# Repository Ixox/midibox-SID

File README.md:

# midibox-SID
PCBs, Panels and firmware for puting a 4 stereo voices midiboxSid in a 1U 19" rack

Contains all files needed for this project : 
http://midibox.org/forums/topic/20008-midibox-sid-rack-1u-project/

SID_CS/
Kicad files for the 1st surface control PCB

SID_CS2/
Kicad files for the 2nd surface control PCB

SID_MB/
Kicad files for the mother board

SID_MIXER/
Kicad files for the mixer PCB

midibox_sid_v2_044_rack1U/
Firmware: Thorsten source code with some modification for the rack 1U PCBs

pfm2_lib.pretty/
Kicad library

shaeffer/
Front Panel Designer files that work with this 1U rack : 
http://www.frontpanels.de/nrg-case-19-enclosures/

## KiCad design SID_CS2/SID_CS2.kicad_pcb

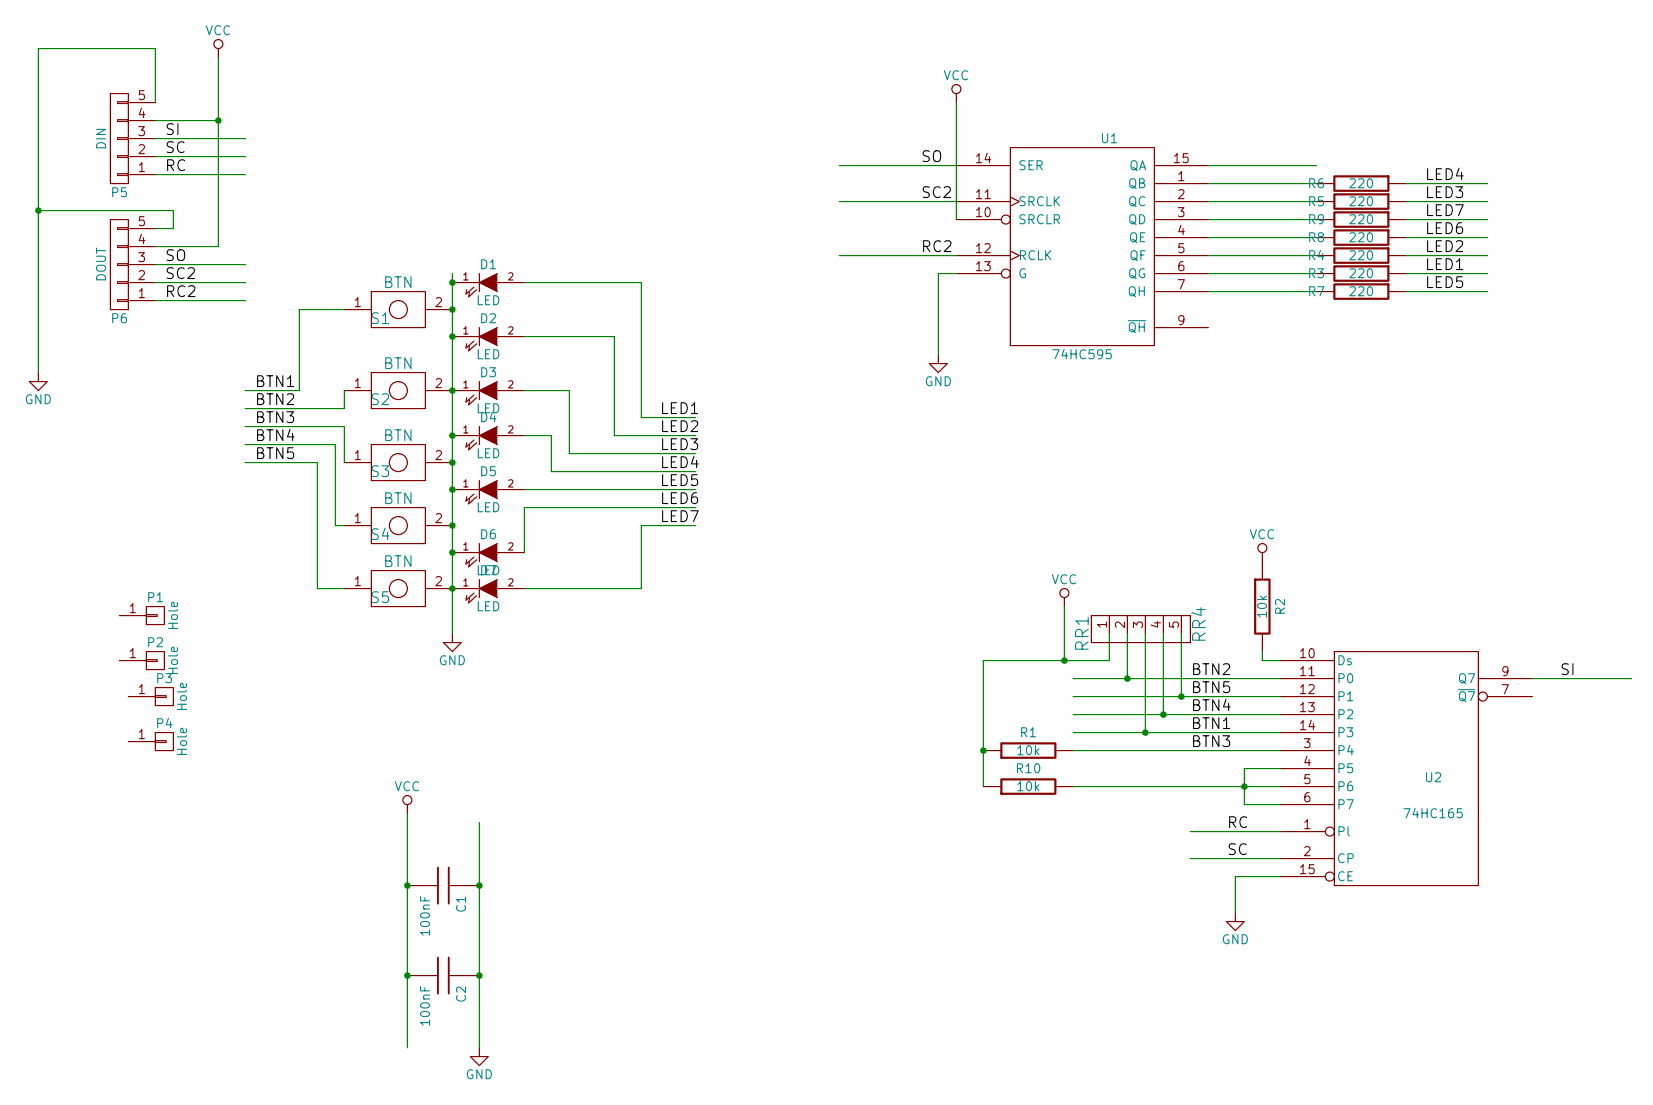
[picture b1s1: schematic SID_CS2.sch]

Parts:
C1, C2: 100nF; C_Disc_D3_P2.5
D1, D2, D3, D4, D5, D6, D7: LED; FMLed2
P1, P2, P3, P4: Hole; MountingHole_3.2mm_M3
P5: DIN; Pin_Header_Straight_1x05
P6: DOUT; Pin_Header_Straight_1x05
R1, R2, R10: 10k; Resistor_Horizontal_RM7mm
R3, R4, R5, R6, R7, R8, R9: 220; Resistor_Horizontal_RM7mm
RR1: RR4; Pin_Header_Straight_1x05
S1, S2, S3, S4, S5: BTN; FMButton2
U1: 74HC595; DIP-16_W7.62mm
U2: 74HC165; DIP-16_W7.62mm

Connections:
/BTN1: RR1.3, S1.1, U2.14 (P3)
/BTN2: RR1.2, S2.1, U2.11 (P0)
/BTN3: R1.2, S3.1, U2.3 (P4)
/BTN4: RR1.4, S4.1, U2.13 (P2)
/BTN5: RR1.5, S5.1, U2.12 (P1)
/LED1: D1.2 (A), R3.1
/LED2: D2.2 (A), R4.1
/LED3: D3.2 (A), R5.1
/LED4: D4.2 (A), R6.1
/LED5: D5.2 (A), R7.1
/LED6: D6.2 (A), R8.1
/LED7: D7.2 (A), R9.1
/RC: P5.1, U2.1 (Pl)
/RC2: P6.1, U1.12 (RCLK)
/SC: P5.2, U2.2 (CP)
/SC2: P6.2, U1.11 (SRCLK)
/SI: P5.3, U2.9 (Q7)
/SO: P6.3, U1.14 (SER)
GND: C1.1, C2.1, D1.1 (K), D2.1 (K), D3.1 (K), D4.1 (K), D5.1 (K), D6.1 (K), D7.1 (K), P5.5, P6.5, S1.2, S2.2, S3.2, S4.2, S5.2, U1.8 (GND), U1.13 (G), U2.8 (GND), U2.15 (CE)
unnamed: R2.2, U2.10 (Ds)
unnamed: R3.2, U1.6 (QG)
unnamed: R4.2, U1.5 (QF)
unnamed: R5.2, U1.2 (QC)
unnamed: R6.2, U1.1 (QB)
unnamed: R7.2, U1.7 (QH)
unnamed: R8.2, U1.4 (QE)
unnamed: R9.2, U1.3 (QD)
unnamed: R10.2, U2.4 (P5), U2.5 (P6), U2.6 (P7)
VCC: C1.2, C2.2, P5.4, P6.4, R1.1, R2.1, R10.1, RR1.1, U1.10 (SRCLR), U1.16 (VCC), U2.16 (VCC)

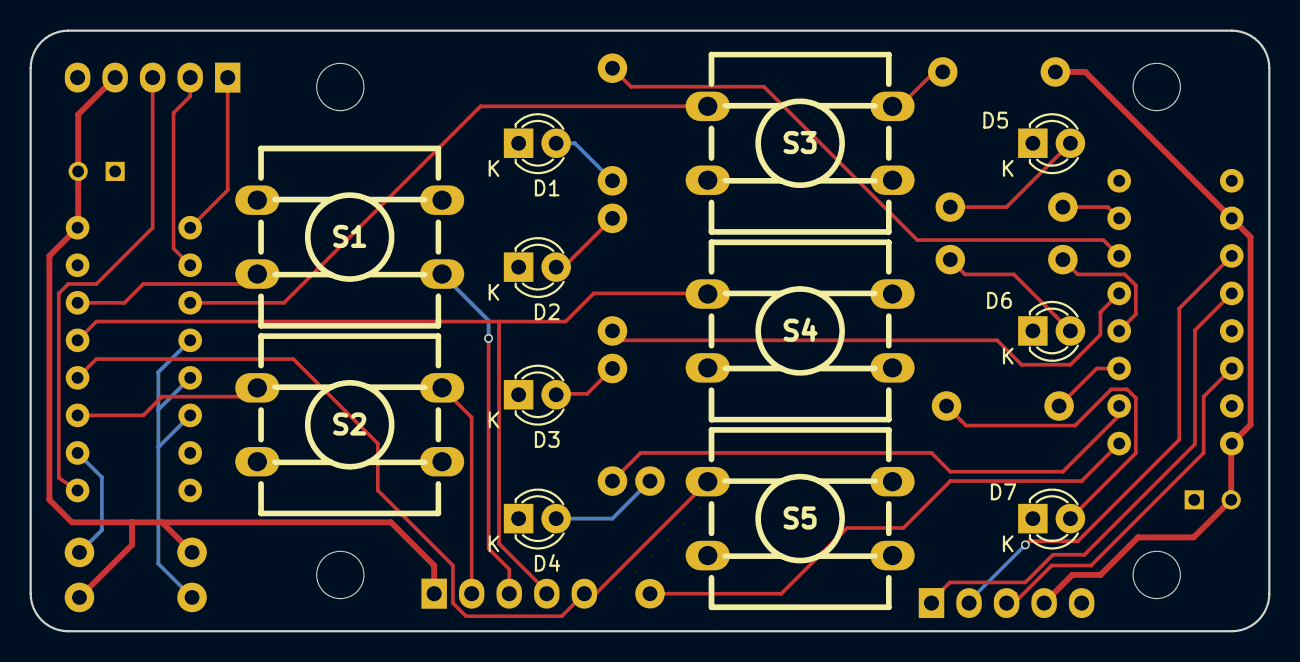
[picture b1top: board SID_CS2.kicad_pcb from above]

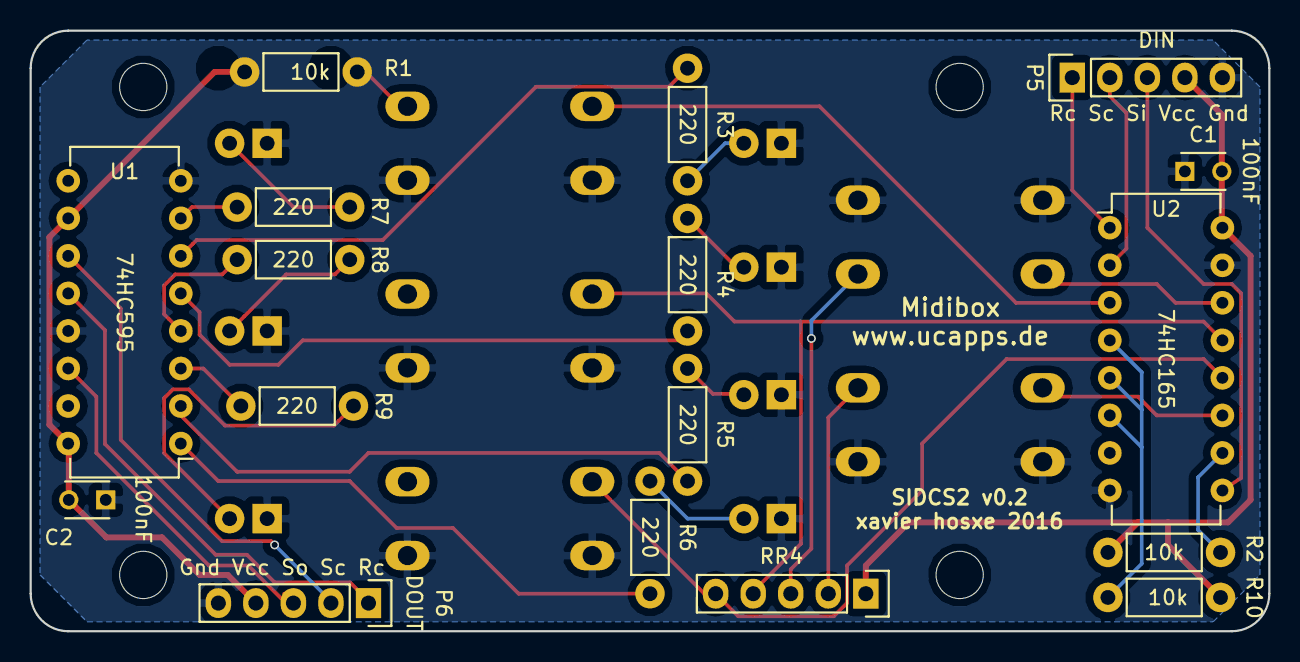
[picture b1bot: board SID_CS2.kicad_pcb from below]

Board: 2 copper layers, 83.8 x 40.6 mm, 33 parts (17 on the bottom side), 29 nets.

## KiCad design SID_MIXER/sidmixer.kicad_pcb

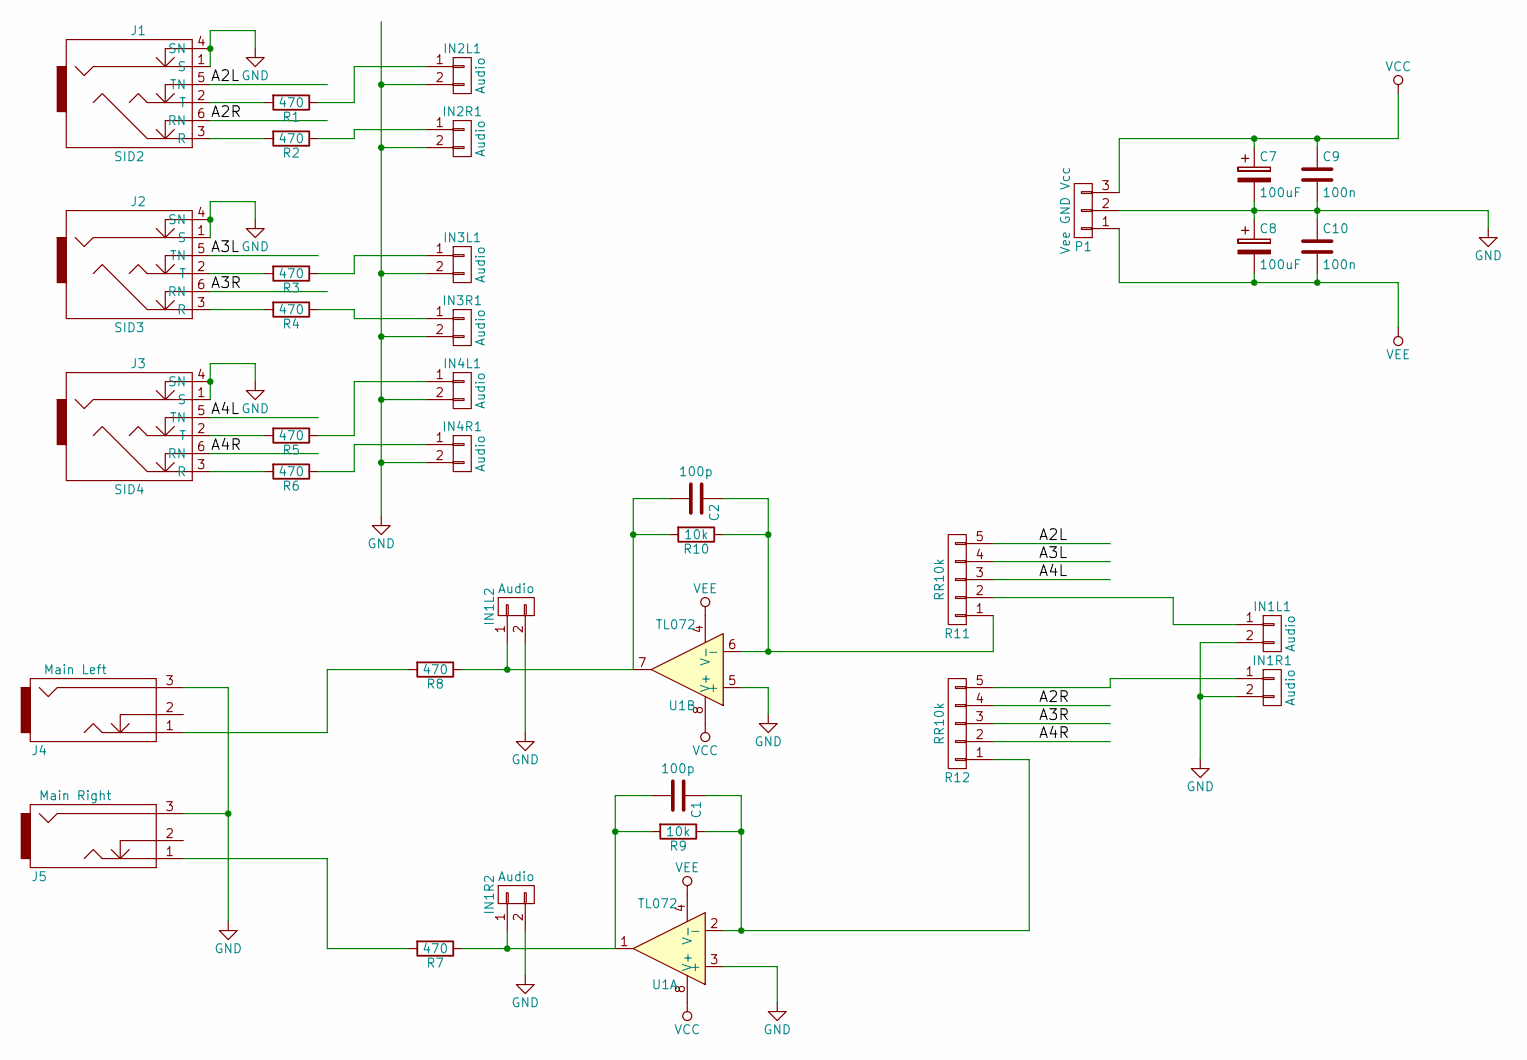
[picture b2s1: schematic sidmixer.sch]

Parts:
C1, C2: 100p; C_Disc_D3_P2.5
C7, C8: 100uF; C_Radial_D6.3_L11.2_P2.5
C9, C10: 100n; C_Disc_D3_P2.5
IN1L1, IN1L2, IN1R1, IN1R2, IN2L1, IN2R1, IN3L1, IN3R1, IN4L1, IN4R1: Audio; Pin_Header_Straight_1x02
J1: SID2; NRJ6HF
J2: SID3; NRJ6HF
J3: SID4; NRJ6HF
J4: Main Left; NRJ4HF
J5: Main Right; NRJ4HF
P1: Vee GND Vcc; Pin_Header_Straight_1x03
R1, R2, R3, R4, R5, R6, R7, R8: 470; Resistor_Horizontal_RM7mm
R9, R10: 10k; Resistor_Horizontal_RM7mm
R11, R12: RR10k; FMRR
U1: TL072; DIP-8_W7.62mm

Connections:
/A2L: J1.5 (TN), R11.5
/A2R: J1.6 (RN), R12.4
/A3L: J2.5 (TN), R11.4
/A3R: J2.6 (RN), R12.3
/A4L: J3.5 (TN), R11.3
/A4R: J3.6 (RN), R12.2
GND: C7.2, C8.1, C9.2, C10.1, IN1L1.2, IN1L2.2, IN1R1.2, IN1R2.2, IN2L1.2, IN2R1.2, IN3L1.2, IN3R1.2, IN4L1.2, IN4R1.2, J1.1 (S), J1.4 (SN), J2.1 (S), J2.4 (SN), J3.1 (S), J3.4 (SN), J4.3, J5.3, P1.2, U1.3 (+), U1.5 (+)
unnamed: C1.1, R9.1, R12.1, U1.2 (-)
unnamed: C1.2, IN1R2.1, R7.1, R9.2, U1.1
unnamed: C2.1, R10.1, R11.1, U1.6 (-)
unnamed: C2.2, IN1L2.1, R8.1, R10.2, U1.7
unnamed: IN1L1.1, R11.2
unnamed: IN1R1.1, R12.5
unnamed: IN2L1.1, R1.1
unnamed: IN2R1.1, R2.1
unnamed: IN3L1.1, R3.1
unnamed: IN3R1.1, R4.1
unnamed: IN4L1.1, R5.1
unnamed: IN4R1.1, R6.1
unnamed: J1.2 (T), R1.2
unnamed: J1.3 (R), R2.2
unnamed: J2.2 (T), R3.2
unnamed: J2.3 (R), R4.2
unnamed: J3.2 (T), R5.2
unnamed: J3.3 (R), R6.2
unnamed: J4.1, R8.2
unnamed: J5.1, R7.2
VCC: C7.1, C9.1, P1.3, U1.8 (V+)
VEE: C8.2, C10.2, P1.1, U1.4 (V-)

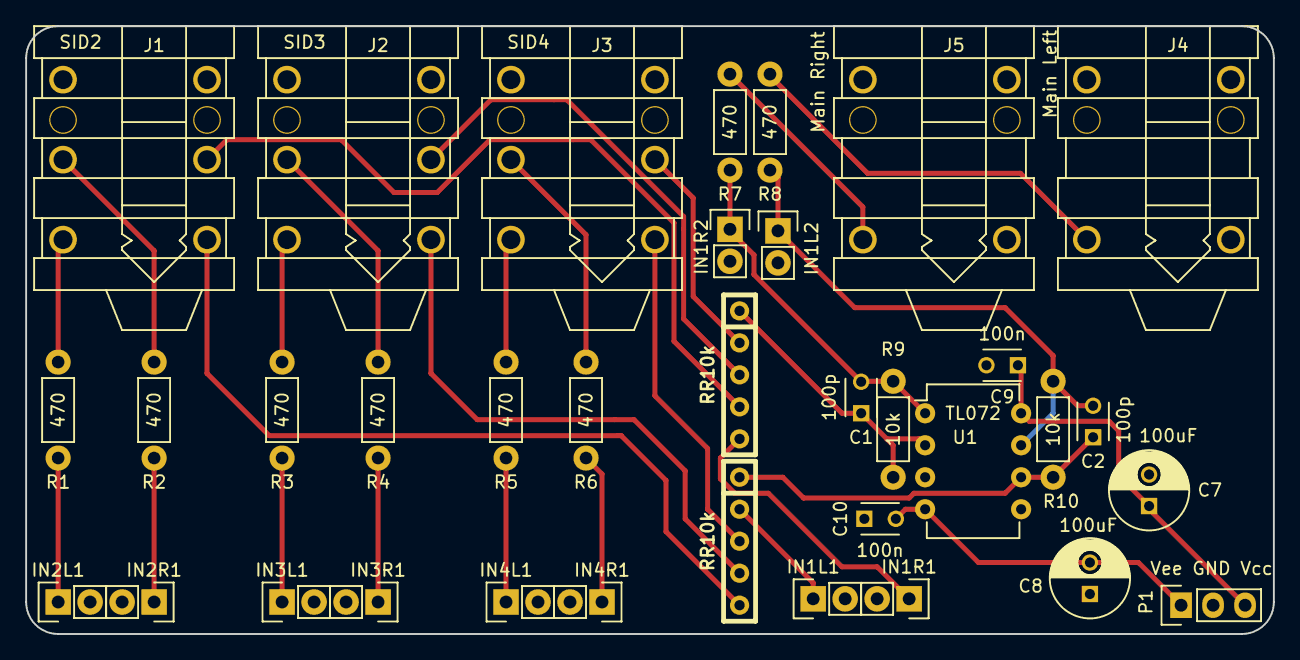
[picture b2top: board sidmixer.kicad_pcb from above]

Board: 2 copper layers, 99.1 x 48.3 mm, 35 parts (0 on the bottom side), 29 nets.

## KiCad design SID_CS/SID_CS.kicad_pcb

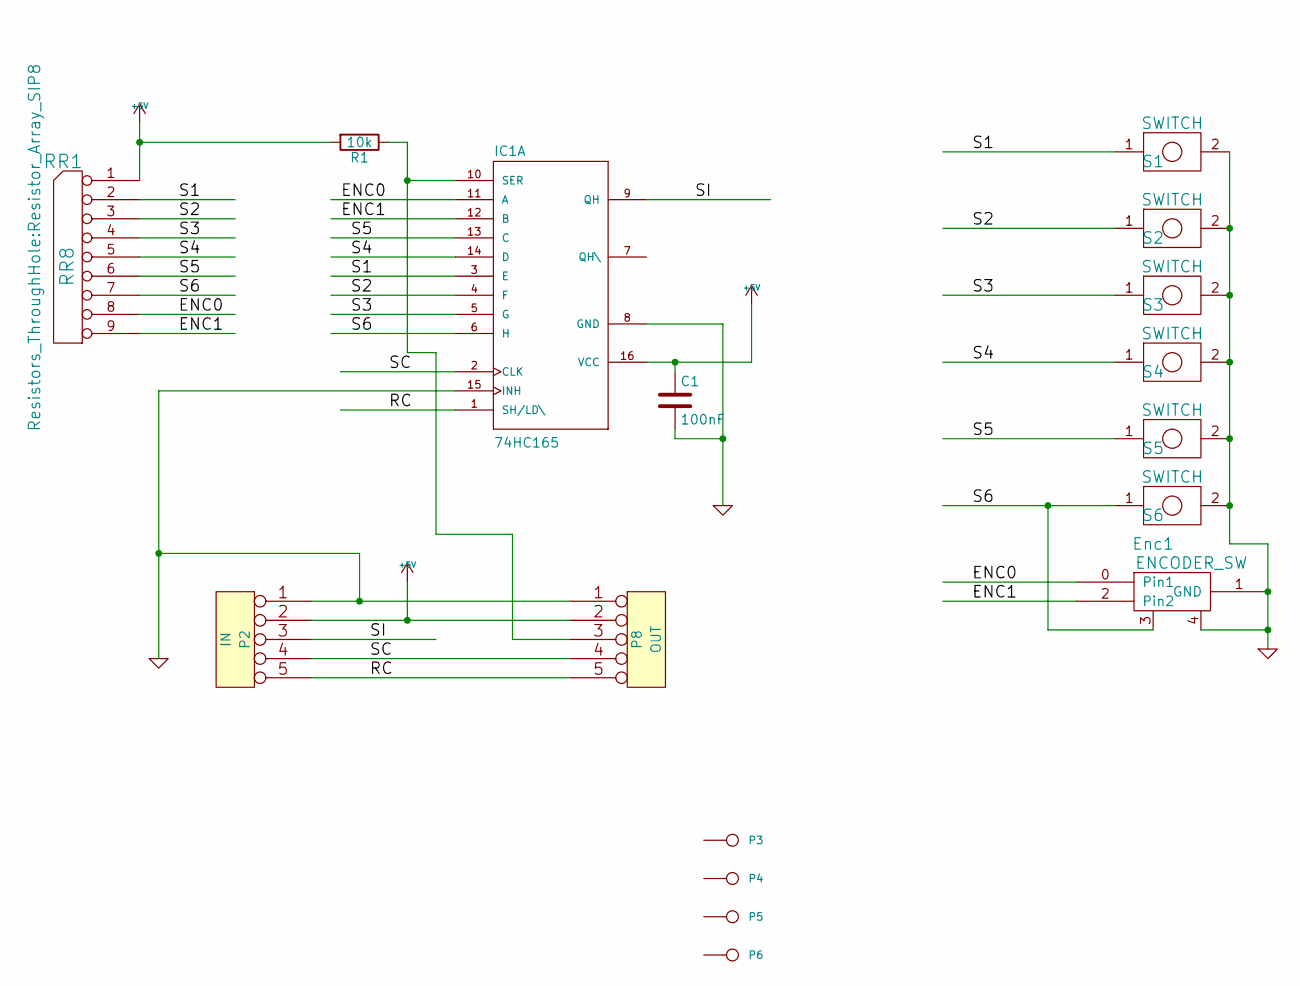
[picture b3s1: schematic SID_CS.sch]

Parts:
C1: 100nF; C_Disc_D3_P2.5
Enc1: ENCODER_SW; FMEncoderWithSwitch2
IC1: 74HC165; DIP-16_W7.62mm_LongPads
P2: IN; Pin_Header_Straight_1x05
P3, P4, P5, P6: CONN_1; MountingHole_3.2mm_M3
P8: OUT; Pin_Header_Straight_1x05
R1: 10k; Resistor_Horizontal_RM7mm
RR1: RR8; Resistor_Array_SIP8
S1, S2, S3, S4, S5, S6: SWITCH; FMButton2

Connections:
+5V: C1.1, IC1.16 (VCC), P2.2, P8.2, R1.2, RR1.1 (COM)
/ENC0: Enc1.0 (Pin1), IC1.11 (A), RR1.8
/ENC1: Enc1.2 (Pin2), IC1.12 (B), RR1.9
/RC: IC1.1 (SH/LD\), P2.5, P8.5
/S1: IC1.3 (E), RR1.2, S1.1
/S2: IC1.4 (F), RR1.3, S2.1
/S3: IC1.5 (G), RR1.4, S3.1
/S4: IC1.14 (D), RR1.5, S4.1
/S5: IC1.13 (C), RR1.6, S5.1
/S6: Enc1.3, IC1.6 (H), RR1.7, S6.1
/SC: IC1.2 (CLK), P2.4, P8.4
/SI: IC1.9 (QH), P2.3
GND: C1.2, Enc1.1 (GND), Enc1.4, IC1.8 (GND), IC1.15 (INH), P2.1, P8.1, S1.2, S2.2, S3.2, S4.2, S5.2, S6.2
unnamed: IC1.10 (SER), P8.3, R1.1

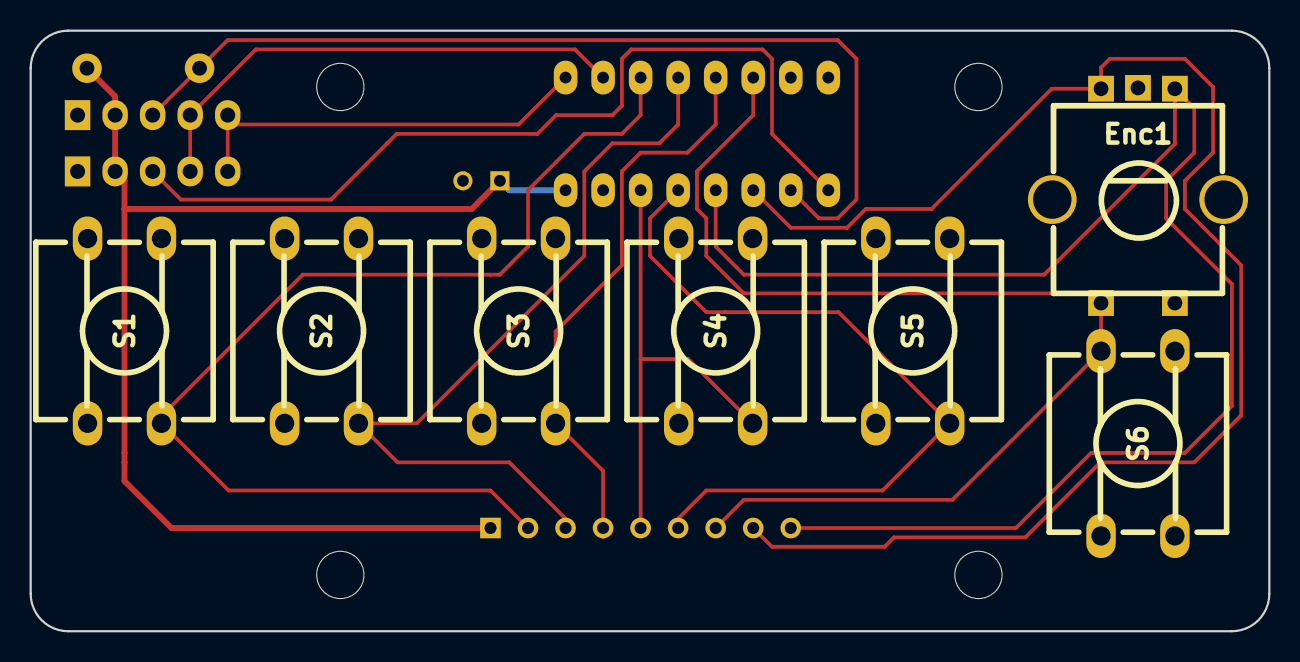
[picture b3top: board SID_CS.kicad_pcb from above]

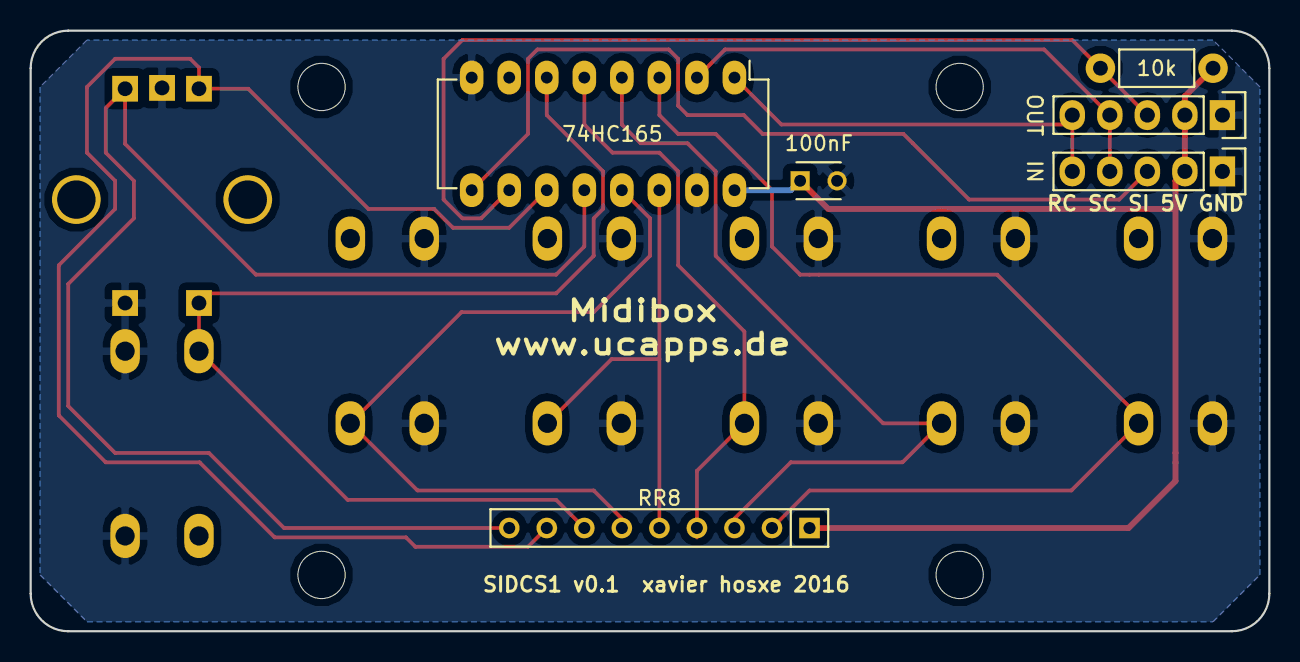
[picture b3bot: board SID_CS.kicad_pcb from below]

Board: 2 copper layers, 83.8 x 40.6 mm, 17 parts (6 on the bottom side), 14 nets.

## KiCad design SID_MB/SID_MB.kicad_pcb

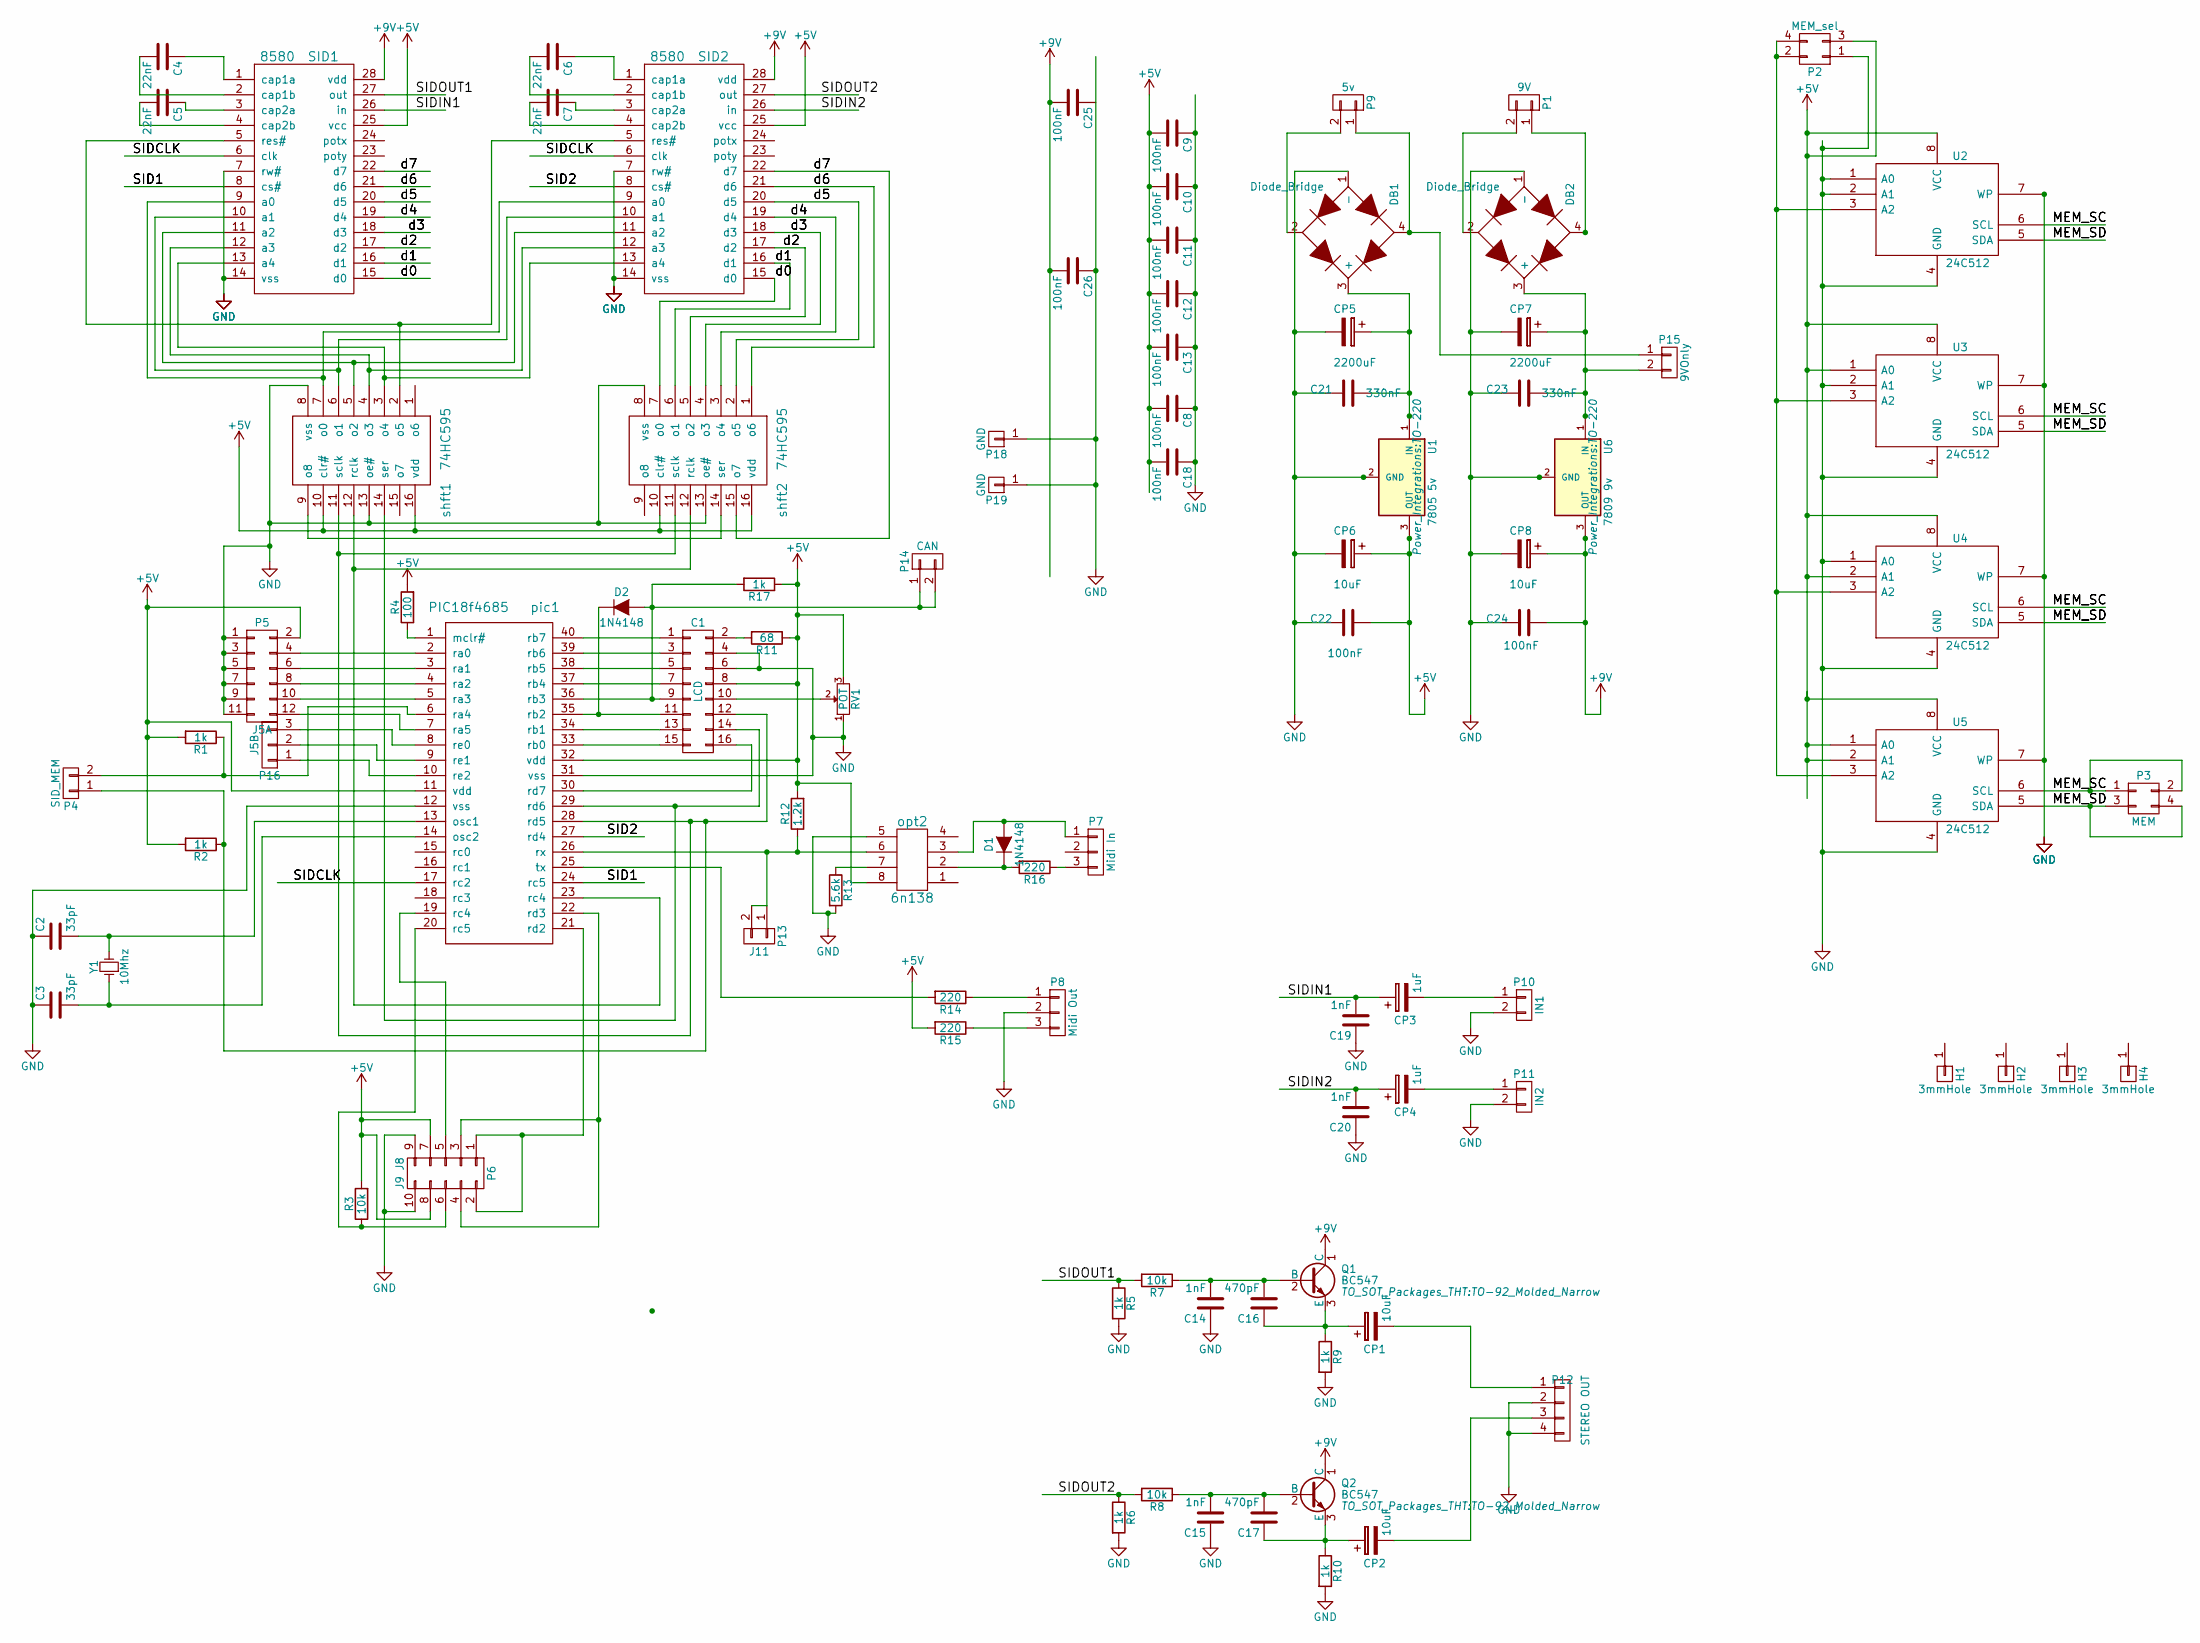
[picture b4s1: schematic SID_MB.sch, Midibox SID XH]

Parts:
C1: LCD; Pin_Header_Straight_2x08
C2, C3: 33pF; C_Rect_L4_W2.5_P2.5
C4, C5, C6, C7: 22nF; C_Rect_L4_W2.5_P2.5
C8, C9, C10, C11, C12, C13, C18, C22, C24, C25, C26: 100nF; C_Rect_L4_W2.5_P2.5
C14, C15, C19, C20: 1nF; C_Rect_L4_W2.5_P2.5
C16, C17: 470pF; C_Rect_L4_W2.5_P2.5
C21, C23: 330nF; C_Rect_L4_W2.5_P2.5
CP1, CP2, CP6, CP8: 10uF; C_Radial_D5_L6_P2.5
CP3, CP4: 1uF; C_Radial_D5_L6_P2.5
CP5, CP7: 2200uF; C_Radial_D12.5_L25_P5
D1, D2: 1N4148; Diode_DO-35_SOD27_Horizontal_RM10
DB1, DB2: Diode_Bridge; Bridge-rond
H1, H2, H3, H4: 3mmHole; MountingHole_3.2mm_M3
P1: 9V; bornier2
P2: MEM_sel; Pin_Header_Straight_2x02
P3: MEM; Pin_Header_Straight_2x02
P4: SID_MEM; Pin_Header_Straight_1x02
P5: J5A; Pin_Header_Straight_2x06
P6: J9 J8; Pin_Header_Straight_2x05
P7: Midi In; Pin_Header_Straight_1x03
P8: Midi Out; Pin_Header_Straight_1x03
P9: 5v; bornier2
P10: IN1; Pin_Header_Straight_1x02
P11: IN2; Pin_Header_Straight_1x02
P12: STEREO OUT; Pin_Header_Straight_1x04
P13: J11; Pin_Header_Straight_1x02
P14: CAN; Pin_Header_Straight_1x02
P15: 9VOnly; Pin_Header_Straight_1x02
P16: J5B; Pin_Header_Straight_1x03
P18, P19: GND; Pin_Header_Straight_1x01
Q1, Q2: BC547; TO-92_Molded_Narrow
R1, R2, R5, R6, R9, R10, R17: 1k; Resistor_Horizontal_RM7mm
R3, R7, R8: 10k; Resistor_Horizontal_RM7mm
R4: 100; Resistor_Horizontal_RM7mm
R11: 68; Resistor_Horizontal_RM7mm
R12: 1.2k; Resistor_Horizontal_RM7mm
R13: 5.6k; Resistor_Horizontal_RM7mm
R14, R15, R16: 220; Resistor_Horizontal_RM7mm
RV1: POT; FMRV
SID1, SID2: 8580; DIP-28_W15.24mm_LongPads
U1: 7805 5v; TO-220
U2, U3, U4, U5: 24C512; DIP-8_W7.62mm
U6: 7809 9v; TO-220
Y1: 10Mhz; Crystal_HC49-U_Vertical
opt2: 6n138; DIP-8_W7.62mm
pic1: PIC18f4685; DIP-40_W15.24mm
shft1, shft2: 74HC595; DIP-16_W7.62mm_LongPads

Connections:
+5V: C1.8, C8.2, C9.2, C10.2, C11.2, C12.2, C13.2, C18.2, C22.2, CP6.1, P2.3, P5.2, P6.7, P6.8, R1.2, R2.2, R3.2, R4.2, R11.1, R12.2, R15.2, R17.1, RV1.3, SID1.25 (vcc), SID2.25 (vcc), U1.3 (OUT), U2.8 (VCC), U3.1 (A0), U3.8 (VCC), U4.2 (A1), U4.8 (VCC), U5.1 (A0), U5.2 (A1), U5.8 (VCC), opt2.8, pic1.11 (vdd), pic1.32 (vdd), shft1.10 (clr#), shft1.16 (vdd), shft2.10 (clr#), shft2.16 (vdd)
+9V: C24.2, C25.2, C26.2, CP8.1, Q1.1 (C), Q2.1 (C), SID1.28 (vdd), SID2.28 (vdd), U6.3 (OUT)
/MEM_SC: P3.1, P3.2, U2.6 (SCL), U3.6 (SCL), U4.6 (SCL), U5.6 (SCL)
/MEM_SD: P3.3, P3.4, U2.5 (SDA), U3.5 (SDA), U4.5 (SDA), U5.5 (SDA)
/SID1: SID1.8 (cs#), pic1.24 (rc5)
/SID2: SID2.8 (cs#), pic1.27 (rd4)
/SIDCLK: SID1.6 (clk), SID2.6 (clk), pic1.17 (rc2)
/SIDIN1: C19.2, CP3.1, SID1.26 (in)
/SIDIN2: C20.2, CP4.1, SID2.26 (in)
/SIDOUT1: R5.1, R7.2, SID1.27 (out)
/SIDOUT2: R6.1, R8.2, SID2.27 (out)
/d0: SID1.15 (d0), SID2.15 (d0), shft2.7 (o0)
/d1: SID1.16 (d1), SID2.16 (d1), shft2.6 (o1)
/d2: SID1.17 (d2), SID2.17 (d2), shft2.5 (o2)
/d3: SID1.18 (d3), SID2.18 (d3), shft2.4 (o3)
/d4: SID1.19 (d4), SID2.19 (d4), shft2.3 (o4)
/d5: SID1.20 (d5), SID2.20 (d5), shft2.2 (o5)
/d6: SID1.21 (d6), SID2.21 (d6), shft2.1 (o6)
/d7: SID1.22 (d7), SID2.22 (d7), shft2.15 (o7)
GND: C1.4, C1.6, C2.1, C3.1, C8.1, C9.1, C10.1, C11.1, C12.1, C13.1, C14.1, C15.1, C18.1, C19.1, C20.1, C21.1, C22.1, C23.1, C24.1, C26.1, CP5.2, CP6.2, CP7.2, CP8.2, DB1.1 (-), DB2.1 (-), P2.1, P5.1, P5.3, P5.5, P5.7, P5.9, P5.11, P6.9, P6.10, P8.2, P10.2, P11.2, P12.2, P12.4, P18.1, P19.1, R5.2, R6.2, R9.2, R10.2, R13.2, RV1.1, SID1.7 (rw#), SID1.14 (vss), SID2.7 (rw#), SID2.14 (vss), U1.2 (GND), U2.1 (A0), U2.2 (A1), U2.4 (GND), U2.7 (WP), U3.2 (A1), U3.4 (GND), U3.7 (WP), U4.1 (A0), U4.4 (GND), U4.7 (WP), U5.4 (GND), U5.7 (WP), U6.2 (GND), opt2.5, pic1.12 (vss), pic1.31 (vss), shft1.8 (vss), shft1.13 (oe#), shft2.8 (vss), shft2.13 (oe#)
unnamed: C1.1, pic1.40 (rb7)
unnamed: C1.2, R11.2
unnamed: C1.3, pic1.39 (rb6)
unnamed: C1.5, pic1.38 (rb5)
unnamed: C1.7, pic1.37 (rb4)
unnamed: C1.9, D2.2 (A), P14.1, P14.2, R17.2, pic1.36 (rb3)
unnamed: C1.10, RV1.2
unnamed: C1.11, D2.1 (K), pic1.35 (rb2)
unnamed: C1.12, P4.1, R2.1, pic1.28 (rd5), shft1.11 (sclk), shft2.11 (sclk)
unnamed: C1.13, pic1.34 (rb1)
unnamed: C1.14, pic1.29 (rd6), shft1.14 (ser)
unnamed: C1.15, pic1.33 (rb0)
unnamed: C1.16, pic1.30 (rd7)
unnamed: C2.2, Y1.2, pic1.13 (osc1)
unnamed: C3.2, Y1.1, pic1.14 (osc2)
unnamed: C4.1, SID1.1 (cap1a)
unnamed: C4.2, SID1.2 (cap1b)
unnamed: C5.1, SID1.3 (cap2a)
unnamed: C5.2, SID1.4 (cap2b)
unnamed: C6.1, SID2.1 (cap1a)
unnamed: C6.2, SID2.2 (cap1b)
unnamed: C7.1, SID2.3 (cap2a)
unnamed: C7.2, SID2.4 (cap2b)
unnamed: C14.2, C16.2, Q1.2 (B), R7.1
unnamed: C15.2, C17.2, Q2.2 (B), R8.1
unnamed: C16.1, CP1.1, Q1.3 (E), R9.1
unnamed: C17.1, CP2.1, Q2.3 (E), R10.1
unnamed: C21.2, CP5.1, DB1.3 (+), U1.1 (IN)
unnamed: C23.2, CP7.1, DB2.3 (+), P15.2, U6.1 (IN)
unnamed: CP1.2, P12.1
unnamed: CP2.2, P12.3
unnamed: CP3.2, P10.1
unnamed: CP4.2, P11.1
unnamed: D1.1 (K), R16.2, opt2.2
unnamed: D1.2 (A), P7.1, opt2.3
unnamed: DB1.2, P9.2
unnamed: DB1.4, P9.1, P15.1
unnamed: DB2.2, P1.2
unnamed: DB2.4, P1.1
unnamed: P2.2, P2.4, U2.3 (A2), U3.3 (A2), U4.3 (A2), U5.3 (A2)
unnamed: P4.2, R1.1, pic1.6 (ra4)
unnamed: P5.4, pic1.2 (ra0)
unnamed: P5.6, pic1.3 (ra1)
unnamed: P5.8, pic1.4 (ra2)
unnamed: P5.10, pic1.5 (ra3)
unnamed: P5.12, pic1.7 (ra5)
unnamed: P6.1, P6.2, pic1.21 (rd2)
unnamed: P6.3, P6.4, pic1.22 (rd3)
unnamed: P6.5, pic1.19 (rc4)
unnamed: P6.6, R3.1, pic1.20 (rc5)
unnamed: P7.3, R16.1
unnamed: P8.1, R14.1
unnamed: P8.3, R15.1
unnamed: P13.1, P13.2, R12.1, opt2.6, pic1.26 (rx)
unnamed: P16.1, pic1.10 (re2)
unnamed: P16.2, pic1.9 (re1)
unnamed: P16.3, pic1.8 (re0)
unnamed: R4.1, pic1.1 (mclr#)
unnamed: R13.1, opt2.7
unnamed: R14.2, pic1.25 (tx)
unnamed: SID1.5 (res#), SID2.5 (res#), shft1.2 (o5)
unnamed: SID1.9 (a0), SID2.9 (a0), shft1.7 (o0)
unnamed: SID1.10 (a1), SID2.10 (a1), shft1.6 (o1)
unnamed: SID1.11 (a2), SID2.11 (a2), shft1.5 (o2)
unnamed: SID1.12 (a3), SID2.12 (a3), shft1.4 (o3)
unnamed: SID1.13 (a4), SID2.13 (a4), shft1.3 (o4)
unnamed: pic1.23 (rc4), shft1.12 (rclk), shft2.12 (rclk)
unnamed: shft1.9 (o8), shft2.14 (ser)

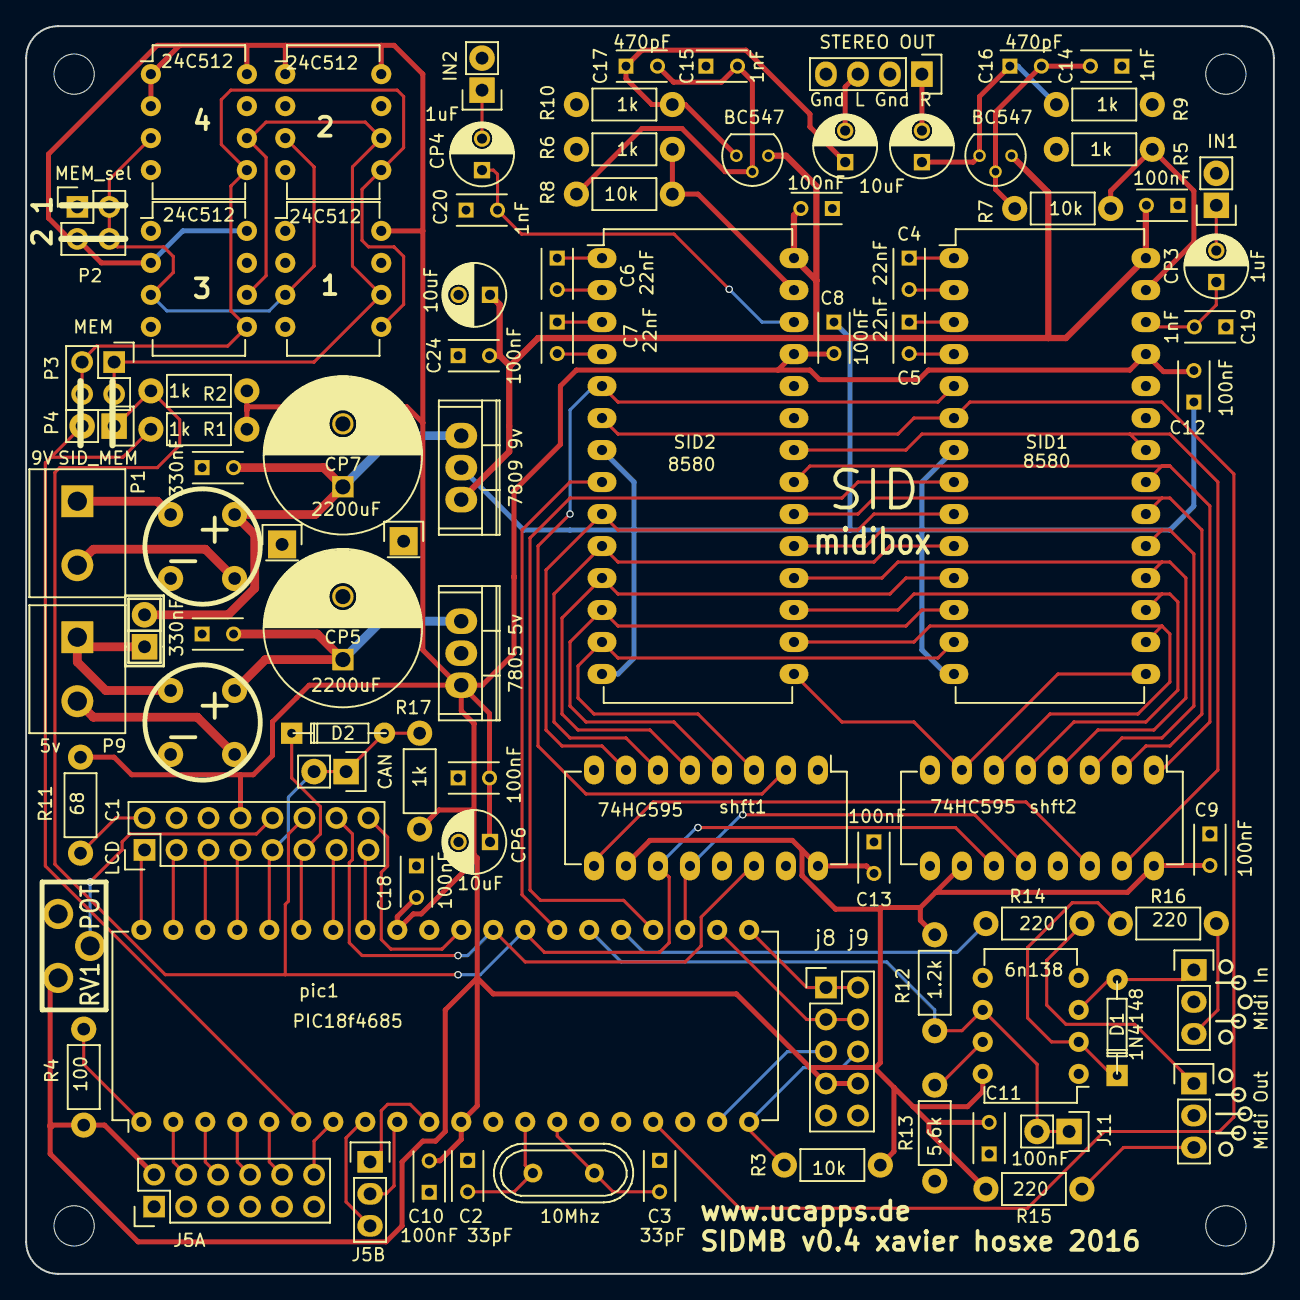
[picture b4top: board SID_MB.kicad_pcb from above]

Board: 2 copper layers, 99.1 x 99.1 mm, 93 parts (0 on the bottom side), 88 nets.

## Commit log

2016-05-25 Better Readme
